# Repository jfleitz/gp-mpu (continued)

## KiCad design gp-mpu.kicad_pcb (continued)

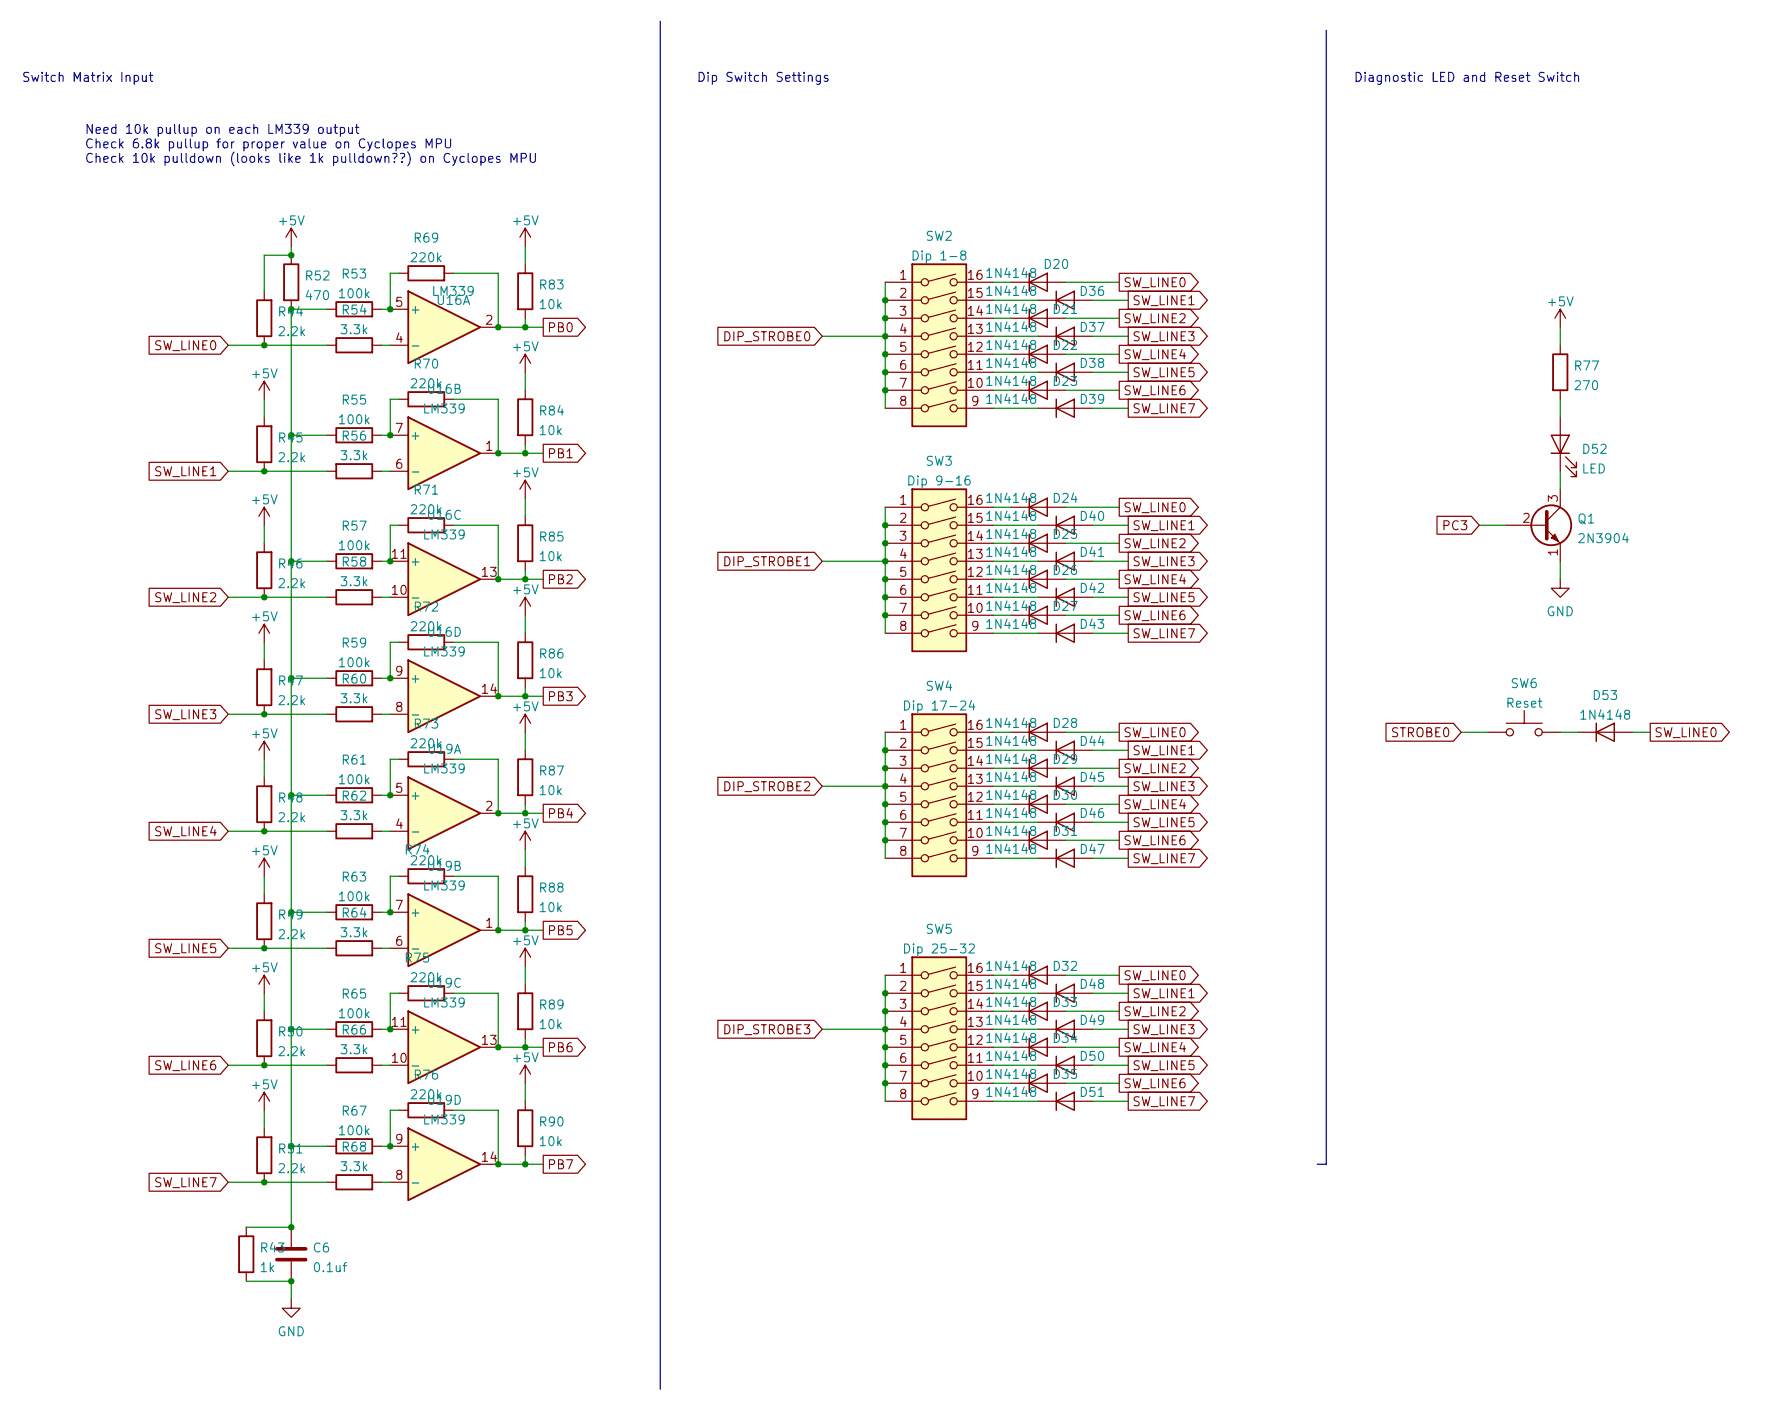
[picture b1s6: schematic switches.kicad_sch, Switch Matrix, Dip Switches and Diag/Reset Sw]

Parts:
C6: 0.1uf; C_Disc_D5.0mm_W2.5mm_P5.00mm
D20, D21, D22, D23, D24, D25, D26, D27, D28, D29, D30, D31, D32, D33, D34, D35, D36, D37, D38, D39, D40, D41, D42, D43, D44, D45, D46, D47, D48, D49, D50, D51, D53: 1N4148; D_DO-35_SOD27_P7.62mm_Horizontal
D52: LED; LED_D3.0mm
Q1: 2N3904; TO-92_Inline
R43: 1k; R_Axial_DIN0207_L6.3mm_D2.5mm_P10.16mm_Horizontal
R44, R45, R46, R47, R48, R49, R50, R51: 2.2k; R_Axial_DIN0207_L6.3mm_D2.5mm_P10.16mm_Horizontal
R52: 470; R_Axial_DIN0207_L6.3mm_D2.5mm_P10.16mm_Horizontal
R53, R55, R57, R59, R61, R63, R65, R67: 100k; R_Axial_DIN0207_L6.3mm_D2.5mm_P10.16mm_Horizontal
R54, R56, R58, R60, R62, R64, R66, R68: 3.3k; R_Axial_DIN0207_L6.3mm_D2.5mm_P10.16mm_Horizontal
R69, R70, R71, R72, R73, R74, R75, R76: 220k; R_Axial_DIN0207_L6.3mm_D2.5mm_P10.16mm_Horizontal
R77: 270; R_Axial_DIN0207_L6.3mm_D2.5mm_P10.16mm_Horizontal
R83, R84, R85, R86, R87, R88, R89, R90: 10k; R_Axial_DIN0207_L6.3mm_D2.5mm_P10.16mm_Horizontal
SW2: Dip 1-8; DIP-16_W7.62mm_LongPads
SW3: Dip 9-16; DIP-16_W7.62mm_LongPads
SW4: Dip 17-24; DIP-16_W7.62mm_LongPads
SW5: Dip 25-32; DIP-16_W7.62mm_LongPads
SW6: Reset; SW_PUSH_6mm_H4.3mm
U16, U19: LM339; DIP-14_W7.62mm_LongPads

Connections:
+5V: R44.2, R45.2, R46.2, R47.2, R48.2, R49.2, R50.2, R51.2, R52.1, R77.1, R83.1, R84.1, R85.1, R86.1, R87.1, R88.1, R89.1, R90.1; also elsewhere on the board
DIP_STROBE0: SW2.1, SW2.2, SW2.3, SW2.4, SW2.5, SW2.6, SW2.7, SW2.8; also elsewhere on the board
DIP_STROBE1: SW3.1, SW3.2, SW3.3, SW3.4, SW3.5, SW3.6, SW3.7, SW3.8; also elsewhere on the board
DIP_STROBE2: SW4.1, SW4.2, SW4.3, SW4.4, SW4.5, SW4.6, SW4.7, SW4.8; also elsewhere on the board
DIP_STROBE3: SW5.1, SW5.2, SW5.3, SW5.4, SW5.5, SW5.6, SW5.7, SW5.8; also elsewhere on the board
GND: C6.2, Q1.1 (E), R43.2; also elsewhere on the board
unnamed: C6.1, R43.1, R52.2, R53.1, R55.1, R57.1, R59.1, R61.1, R63.1, R65.1, R67.1
unnamed: D20.1 (K), SW2.16
unnamed: D21.1 (K), SW2.14
unnamed: D22.1 (K), SW2.12
unnamed: D23.1 (K), SW2.10
unnamed: D24.1 (K), SW3.16
unnamed: D25.1 (K), SW3.14
unnamed: D26.1 (K), SW3.12
unnamed: D27.1 (K), SW3.10
unnamed: D28.1 (K), SW4.16
unnamed: D29.1 (K), SW4.14
unnamed: D30.1 (K), SW4.12
unnamed: D31.1 (K), SW4.10
unnamed: D32.1 (K), SW5.16
unnamed: D33.1 (K), SW5.14
unnamed: D34.1 (K), SW5.12
unnamed: D35.1 (K), SW5.10
unnamed: D36.1 (K), SW2.15
unnamed: D37.1 (K), SW2.13
unnamed: D38.1 (K), SW2.11
unnamed: D39.1 (K), SW2.9
unnamed: D40.1 (K), SW3.15
unnamed: D41.1 (K), SW3.13
unnamed: D42.1 (K), SW3.11
unnamed: D43.1 (K), SW3.9
unnamed: D44.1 (K), SW4.15
unnamed: D45.1 (K), SW4.13
unnamed: D46.1 (K), SW4.11
unnamed: D47.1 (K), SW4.9
unnamed: D48.1 (K), SW5.15
unnamed: D49.1 (K), SW5.13
unnamed: D50.1 (K), SW5.11
unnamed: D51.1 (K), SW5.9
unnamed: D52.1 (K), Q1.3 (C)
unnamed: D52.2 (A), R77.2
unnamed: D53.1 (K), SW6.2
unnamed: R53.2, R69.1, U16.5 (+)
unnamed: R54.2, U16.4 (-)
unnamed: R55.2, R70.1, U16.7 (+)
unnamed: R56.1, U16.6 (-)
unnamed: R57.2, R71.1, U16.11 (+)
unnamed: R58.2, U16.10 (-)
unnamed: R59.2, R72.1, U16.9 (+)
unnamed: R60.2, U16.8 (-)
unnamed: R61.2, R73.1, U19.5 (+)
unnamed: R62.2, U19.4 (-)
unnamed: R63.2, R74.1, U19.7 (+)
unnamed: R64.2, U19.6 (-)
unnamed: R65.2, R75.1, U19.11 (+)
unnamed: R66.2, U19.10 (-)
unnamed: R67.2, R76.1, U19.9 (+)
unnamed: R68.2, U19.8 (-)
PB0: R69.2, R83.2, U16.2; also elsewhere on the board
PB1: R70.2, R84.2, U16.1; also elsewhere on the board
PB2: R71.2, R85.2, U16.13; also elsewhere on the board
PB3: R72.2, R86.2, U16.14; also elsewhere on the board
PB4: R73.2, R87.2, U19.2; also elsewhere on the board
PB5: R74.2, R88.2, U19.1; also elsewhere on the board
PB6: R75.2, R89.2, U19.13; also elsewhere on the board
PB7: R76.2, R90.2, U19.14; also elsewhere on the board
PC3: Q1.2 (B); also elsewhere on the board
STROBE0: SW6.1; also elsewhere on the board
SW_LINE0: D20.2 (A), D24.2 (A), D28.2 (A), D32.2 (A), D53.2 (A), R44.1, R54.1; also elsewhere on the board
SW_LINE1: D36.2 (A), D40.2 (A), D44.2 (A), D48.2 (A), R45.1, R56.2; also elsewhere on the board
SW_LINE2: D21.2 (A), D25.2 (A), D29.2 (A), D33.2 (A), R46.1, R58.1; also elsewhere on the board
SW_LINE3: D37.2 (A), D41.2 (A), D45.2 (A), D49.2 (A), R47.1, R60.1; also elsewhere on the board
SW_LINE4: D22.2 (A), D26.2 (A), D30.2 (A), D34.2 (A), R48.1, R62.1; also elsewhere on the board
SW_LINE5: D38.2 (A), D42.2 (A), D46.2 (A), D50.2 (A), R49.1, R64.1; also elsewhere on the board
SW_LINE6: D23.2 (A), D27.2 (A), D31.2 (A), D35.2 (A), R50.1, R66.1; also elsewhere on the board
SW_LINE7: D39.2 (A), D43.2 (A), D47.2 (A), D51.2 (A), R51.1, R68.1; also elsewhere on the board

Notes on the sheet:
Switch Matrix Input
Need 10k pullup on each LM339 output Check 6.8k pullup for proper value on Cyclopes MPU Check 10k pulldown (looks like 1k pulldown??) on Cyclopes MPU
Diagnostic LED and Reset Switch
Dip Switch Settings

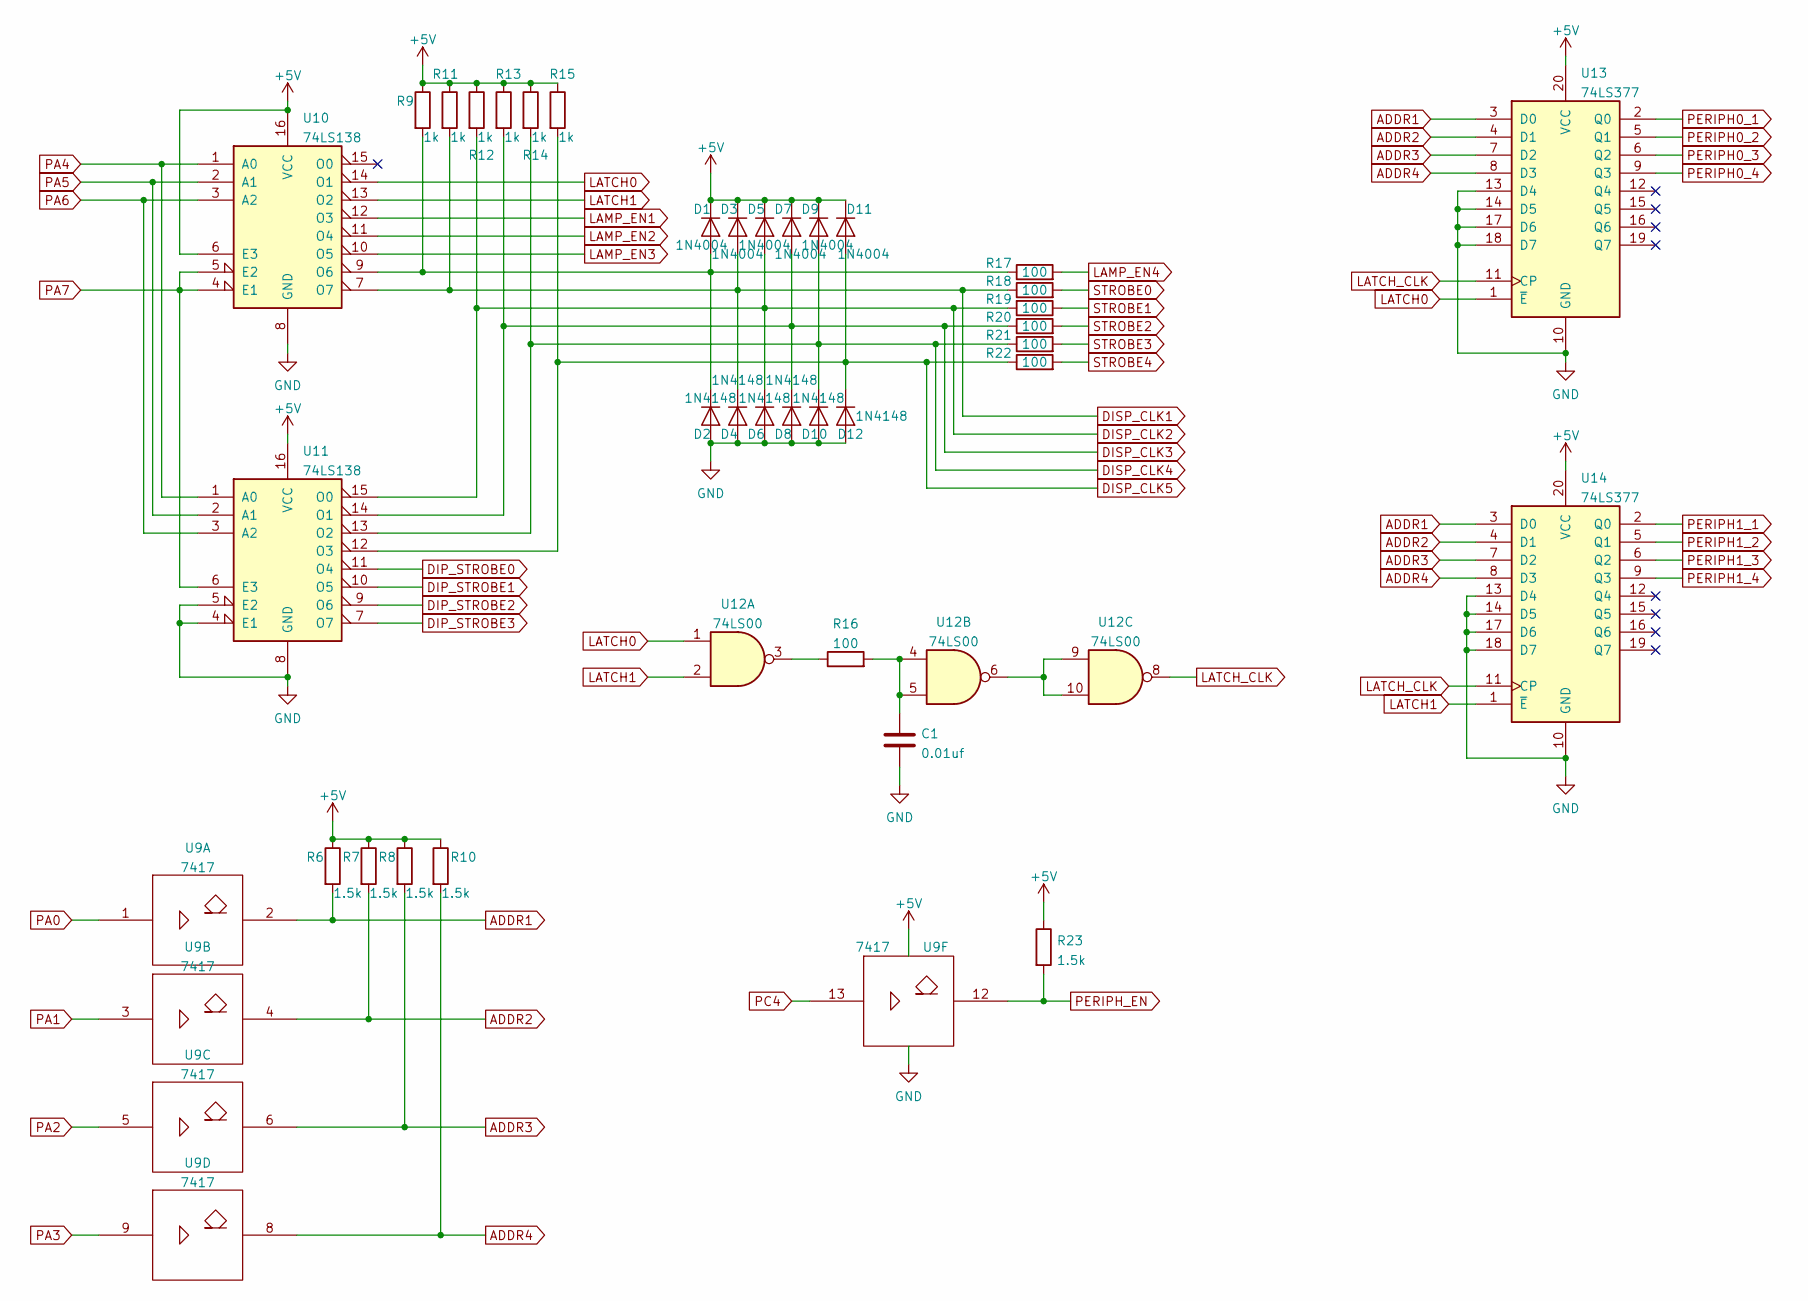
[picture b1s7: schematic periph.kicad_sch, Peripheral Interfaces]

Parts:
C1: 0.01uf; C_Disc_D5.0mm_W2.5mm_P5.00mm
D1, D3, D5, D7, D9, D11: 1N4004; D_DO-41_SOD81_P10.16mm_Horizontal
D2, D4, D6, D8, D10, D12: 1N4148; D_DO-35_SOD27_P7.62mm_Horizontal
R6, R7, R8, R10, R23: 1.5k; R_Axial_DIN0207_L6.3mm_D2.5mm_P10.16mm_Horizontal
R9, R11, R12, R13, R14, R15: 1k; R_Axial_DIN0207_L6.3mm_D2.5mm_P10.16mm_Horizontal
R16, R17, R18, R19, R20, R21, R22: 100; R_Axial_DIN0207_L6.3mm_D2.5mm_P10.16mm_Horizontal
U9: 7417; DIP-14_W7.62mm_LongPads
U10, U11: 74LS138; DIP-16_W7.62mm_LongPads
U12: 74LS00; DIP-14_W7.62mm_LongPads
U13, U14: 74LS377; DIP-20_W7.62mm_LongPads

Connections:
+5V: D1.1 (K), D3.1 (K), D5.1 (K), D7.1 (K), D9.1 (K), D11.1 (K), R6.1, R7.1, R8.1, R9.1, R10.1, R11.1, R12.1, R13.1, R14.1, R15.1, R23.1, U9.14 (Vcc), U10.6 (E3), U10.16 (VCC), U11.16 (VCC), U13.20 (VCC), U14.20 (VCC); also elsewhere on the board
ADDR1: R6.2, U9.2, U13.3 (D0), U14.3 (D0); also elsewhere on the board
ADDR2: R7.2, U9.4, U13.4 (D1), U14.4 (D1); also elsewhere on the board
ADDR3: R8.2, U9.6, U13.7 (D2), U14.7 (D2); also elsewhere on the board
ADDR4: R10.2, U9.8, U13.8 (D3), U14.8 (D3); also elsewhere on the board
DIP_STROBE0: U11.11 (O4); also elsewhere on the board
DIP_STROBE1: U11.10 (O5); also elsewhere on the board
DIP_STROBE2: U11.9 (O6); also elsewhere on the board
DIP_STROBE3: U11.7 (O7); also elsewhere on the board
DISP_CLK1: D3.2 (A), D4.1 (K), R11.2, R18.1, U10.7 (O7); also elsewhere on the board
DISP_CLK2: D5.2 (A), D6.1 (K), R12.2, R19.2, U11.15 (O0); also elsewhere on the board
DISP_CLK3: D7.2 (A), D8.1 (K), R13.2, R20.1, U11.14 (O1); also elsewhere on the board
DISP_CLK4: D9.2 (A), D10.1 (K), R14.2, R21.1, U11.13 (O2); also elsewhere on the board
DISP_CLK5: D11.2 (A), D12.1 (K), R15.2, R22.1, U11.12 (O3); also elsewhere on the board
GND: C1.2, D2.2 (A), D4.2 (A), D6.2 (A), D8.2 (A), D10.2 (A), D12.2 (A), U9.7 (Gnd), U10.8 (GND), U11.4 (E1), U11.5 (E2), U11.8 (GND), U13.10 (GND), U13.13 (D4), U13.14 (D5), U13.17 (D6), U13.18 (D7), U14.10 (GND), U14.13 (D4), U14.14 (D5), U14.17 (D6), U14.18 (D7); also elsewhere on the board
LAMP_EN1: U10.12 (O3); also elsewhere on the board
LAMP_EN2: U10.11 (O4); also elsewhere on the board
LAMP_EN3: U10.10 (O5); also elsewhere on the board
LAMP_EN4: R17.2; also elsewhere on the board
LATCH0: U10.14 (O1), U12.1, U13.1 (~E)
LATCH1: U10.13 (O2), U12.2, U14.1 (~E)
LATCH_CLK: U12.8, U13.11 (CP), U14.11 (CP)
unnamed: C1.1, R16.2, U12.4, U12.5
unnamed: D1.2 (A), D2.1 (K), R9.2, R17.1, U10.9 (O6)
unnamed: R16.1, U12.3
unnamed: U12.6, U12.9, U12.10
PA0: U9.1; also elsewhere on the board
PA1: U9.3; also elsewhere on the board
PA2: U9.5; also elsewhere on the board
PA3: U9.9; also elsewhere on the board
PA4: U10.1 (A0), U11.1 (A0); also elsewhere on the board
PA5: U10.2 (A1), U11.2 (A1); also elsewhere on the board
PA6: U10.3 (A2), U11.3 (A2); also elsewhere on the board
PA7: U10.4 (E1), U10.5 (E2), U11.6 (E3); also elsewhere on the board
PC4: U9.13; also elsewhere on the board
PERIPH0_1: U13.2 (Q0); also elsewhere on the board
PERIPH0_2: U13.5 (Q1); also elsewhere on the board
PERIPH0_3: U13.6 (Q2); also elsewhere on the board
PERIPH0_4: U13.9 (Q3); also elsewhere on the board
PERIPH1_1: U14.2 (Q0); also elsewhere on the board
PERIPH1_2: U14.5 (Q1); also elsewhere on the board
PERIPH1_3: U14.6 (Q2); also elsewhere on the board
PERIPH1_4: U14.9 (Q3); also elsewhere on the board
PERIPH_EN: R23.2, U9.12; also elsewhere on the board
STROBE0: R18.2; also elsewhere on the board
STROBE1: R19.1; also elsewhere on the board
STROBE2: R20.2; also elsewhere on the board
STROBE3: R21.2; also elsewhere on the board
STROBE4: R22.2; also elsewhere on the board

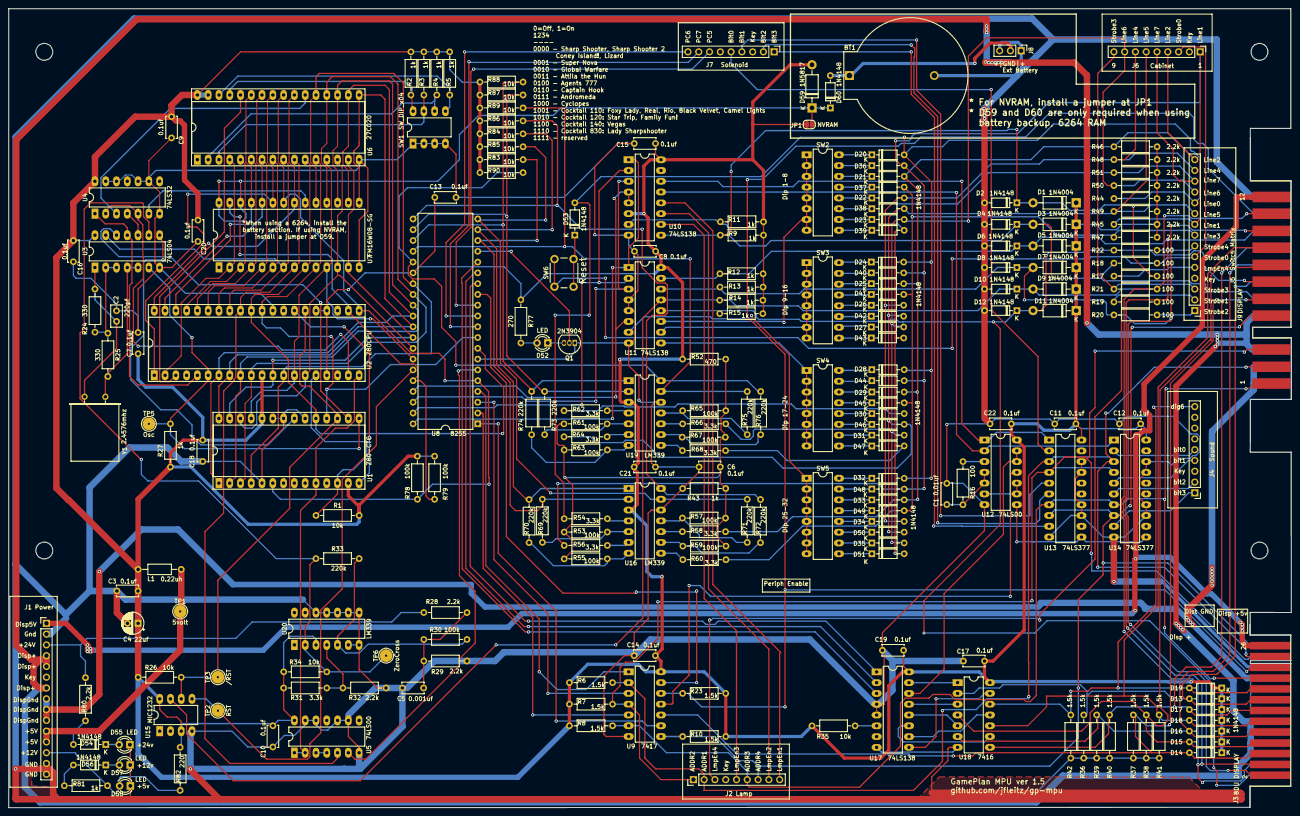
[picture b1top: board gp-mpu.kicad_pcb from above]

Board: 2 copper layers, 302.1 x 188.2 mm, 217 parts (0 on the bottom side), 203 nets.

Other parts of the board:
JP1: NVRAM; SolderJumper-2_P1.3mm_Open_RoundedPad1.0x1.5mm

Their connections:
+5V: JP1.2 (B); also elsewhere on the board
+BATT: JP1.1 (A); also elsewhere on the board

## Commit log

2022-02-19 Ver 1.1
2022-02-19 update ROM image
2022-02-19 update mounting holes
2022-03-04 move key label, mounting holes
2022-04-16 enlarge all vias
2022-04-28 add rom zip
2022-05-12 v1.4
2022-05-12 Add assembly doc
2022-08-27 Update BDU connector
